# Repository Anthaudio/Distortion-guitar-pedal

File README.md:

# Distortion-guitar-pedal
Dans ce projet, nous allons créer une pédale de distortion pour guitare électrique.  
Pour se faire, notre pédale est divisé en deux parties :  
-Un amplificateur du signal d'entrée avec un gain réglable à l'aide d'un potentiomètre  
-Un étage d'écrêtage du signal réalisé à l'aide de diodes.  
Pour ce projet, la pédale doit être alimentée en 9V.  
https://barbarach.com/mxr-distortion-plus-on-breadboard/

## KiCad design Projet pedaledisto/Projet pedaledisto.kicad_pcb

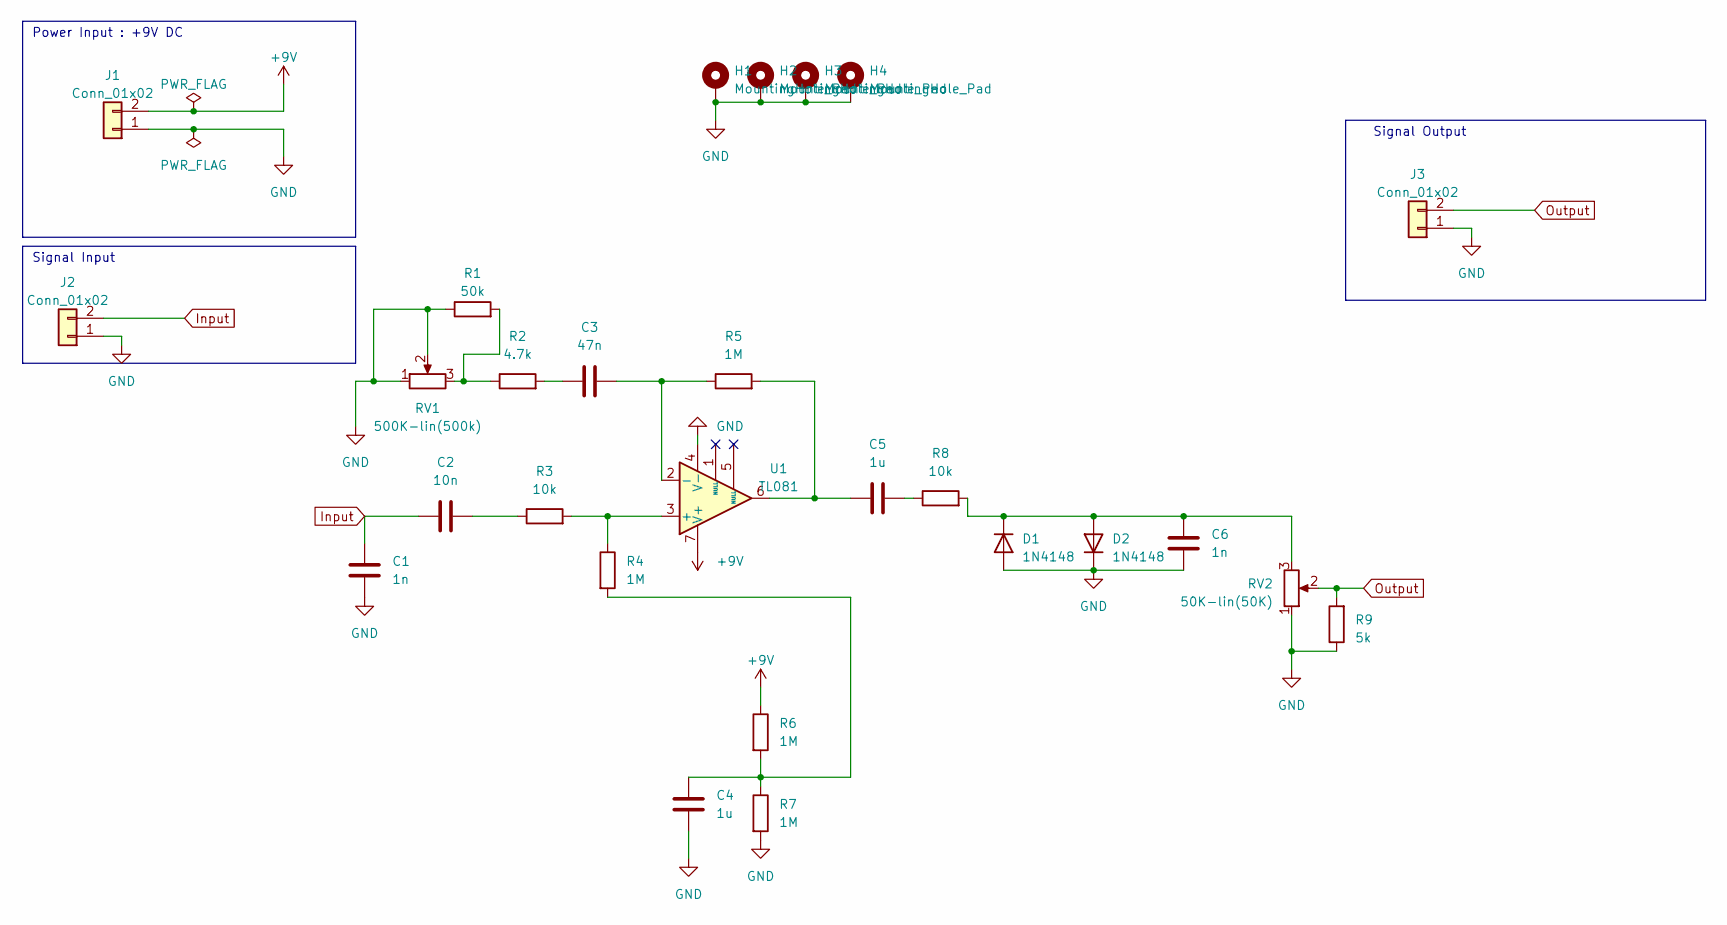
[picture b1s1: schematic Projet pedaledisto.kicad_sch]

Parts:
C1, C6: 1n; C_0603_1608Metric_Pad1.08x0.95mm_HandSolder
C2: 10n; C_0603_1608Metric_Pad1.08x0.95mm_HandSolder
C3: 47n; C_0603_1608Metric_Pad1.08x0.95mm_HandSolder
C4, C5: 1u; C_0603_1608Metric_Pad1.08x0.95mm_HandSolder
D1, D2: 1N4148; D_0603_1608Metric_Pad1.05x0.95mm_HandSolder
H1, H2, H3, H4: MountingHole_Pad; MountingHole_3.2mm_M3_Pad_Via
J1, J2, J3: Conn_01x02; JST_XH_B2B-XH-A_1x02_P2.50mm_Vertical
R1: 50k; R_0603_1608Metric_Pad0.98x0.95mm_HandSolder
R2: 4.7k; R_0603_1608Metric_Pad0.98x0.95mm_HandSolder
R3, R8: 10k; R_0603_1608Metric_Pad0.98x0.95mm_HandSolder
R4, R5, R6, R7: 1M; R_0603_1608Metric_Pad0.98x0.95mm_HandSolder
R9: 5k; R_0603_1608Metric_Pad0.98x0.95mm_HandSolder
RV1: 500K-lin(500k); JST_XH_B3B-XH-A_1x03_P2.50mm_Vertical
RV2: 50K-lin(50K); JST_XH_B3B-XH-A_1x03_P2.50mm_Vertical
U1: TL081; SOIC-8-1EP_3.9x4.9mm_P1.27mm_EP2.29x3mm

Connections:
+9V: J1.2, R6.1, U1.7 (V+)
GND: C1.2, C4.2, C6.2, D1.2 (A), D2.1 (K), H1.1, H2.1, H3.1, H4.1, J1.1, J2.1, J3.1, R1.1, R7.2, R9.1, RV1.1, RV1.2, RV2.1, U1.4 (V-)
Input: C1.1, C2.1, J2.2
unnamed: C2.2, R3.1
unnamed: C3.1, R2.2
unnamed: C4.1, R4.2, R6.2, R7.1
unnamed: C5.1, R5.2, U1.6
unnamed: C5.2, R8.1
unnamed: C6.1, D1.1 (K), D2.2 (A), R8.2, RV2.3
unnamed: R1.2, R2.1, RV1.3
unnamed: R3.2, R4.1, U1.3 (+)
unnamed: C3.2, R5.1, U1.2 (-)
Output: J3.2, R9.2, RV2.2

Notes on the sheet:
Signal Output
Signal Input
Power Input : +9V DC

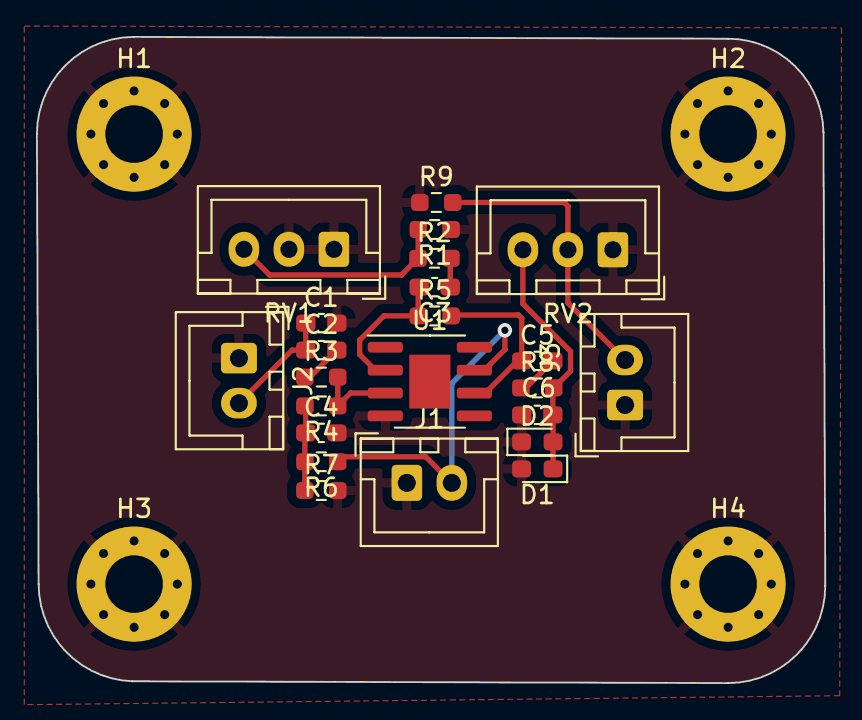
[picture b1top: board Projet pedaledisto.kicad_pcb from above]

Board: 2 copper layers, 43.8 x 35.9 mm, 27 parts (0 on the bottom side), 13 nets.
